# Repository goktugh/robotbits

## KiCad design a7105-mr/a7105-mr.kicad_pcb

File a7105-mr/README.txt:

A7105-MR

This board is a copy (reverse engineerd) of the MD7105-SY module
made by unknown Chinese company. No schematic is publicly available
so I've tried to copy the datasheet and the layout in the modules.

The reason for reverse engineering the board is to create a compatibe copy
with a much smaller crystal, as the original is absolutely huge.

I'm not completely sure what the board thickness needs to be, it is a thin 
pcb, either 0.8mm or 1.0mm (need to check with some calipers maybe?)

I don't know exactly what values all the capacitors / resistor / inductors are.
Finding the values is difficult because they are 0402 smd packages and mounted on the board.

The a7105 datasheet contains a schematic which is mostly similar to the one here. Some parts
are missed out though (presumably they are not needed, the original modules 
work properly, after all)

Two of the inductors are made using PCB traces (microstrip inductors) and
their inductance is very approximate.

A svg reverse engineering the board is in ../a7105_module

Sorry to whoever's intellectual property is taken with this, but I don't expect they
get much royalty anyway on a module which sells at < $2

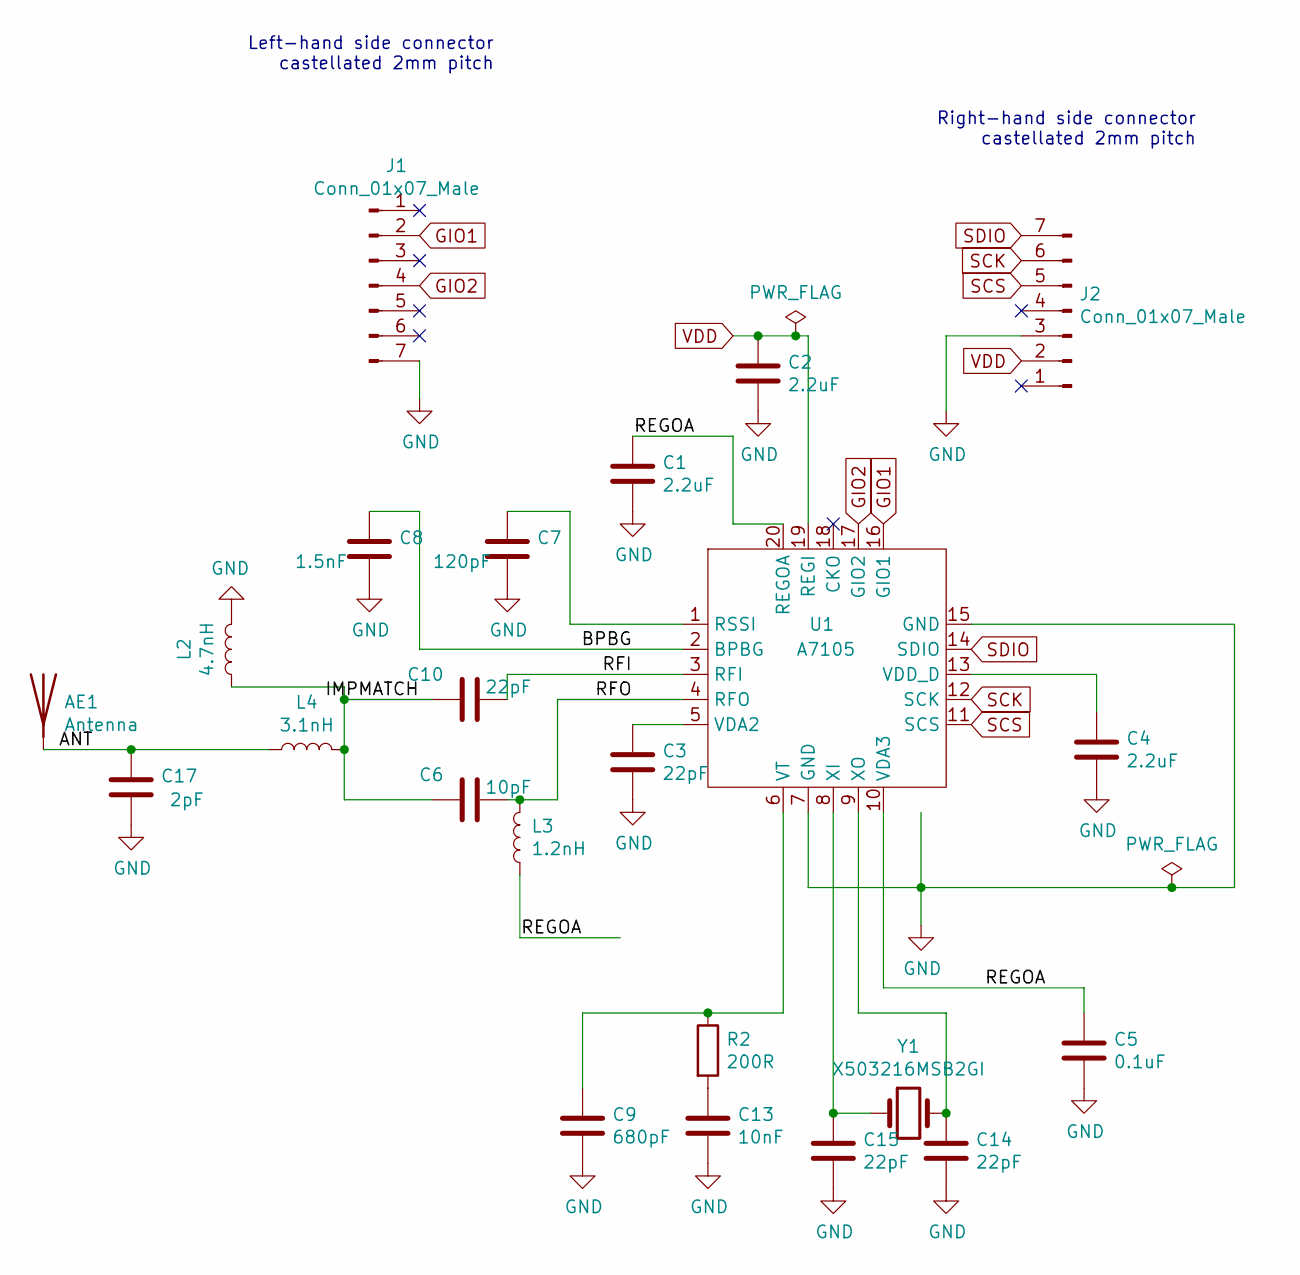
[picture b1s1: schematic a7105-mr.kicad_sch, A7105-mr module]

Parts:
AE1: Antenna; MIFA2
C1, C2, C4: 2.2uF; C_0402_1005Metric; LCSC C12530
C3, C10, C14, C15: 22pF; C_0402_1005Metric; LCSC C1555
C5: 0.1uF; C_0402_1005Metric; LCSC C1525
C6: 10pF; C_0402_1005Metric; LCSC C32949
C7: 120pF; C_0402_1005Metric; LCSC C76949
C8: 1.5nF; C_0402_1005Metric; LCSC C23967
C9: 680pF; C_0402_1005Metric; LCSC C307451
C13: 10nF; C_0402_1005Metric; LCSC C15195
C17: 2pF; C_0402_1005Metric; LCSC C1558
J1, J2: Conn_01x07_Male; castellatedpads_7
L2: 4.7nH; L_0402_1005Metric; LCSC C13595
L3: 1.2nH; mw_inductor_1nh
L4: 3.1nH; mw_inductor_3nh
R2: 200R; R_0402_1005Metric; LCSC C25087
U1: A7105; a7105-QFN-20; LCSC C126376
Y1: X503216MSB2GI; Crystal_SMD_5032-2Pin_5.0x3.2mm; LCSC C112572

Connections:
/ANT: AE1.1 (A), C17.1, L4.1
/BPBG: C8.1, U1.2 (BPBG)
/IMPMATCH: C6.1, C10.1, L2.1, L4.2
/REGOA: C1.1, C5.1, L3.1, U1.10 (VDA3), U1.20 (REGOA)
/RFI: C10.2, U1.3 (RFI)
/RFO: C6.2, L3.2, U1.4 (RFO)
GIO1: J1.2, U1.16 (GIO1)
GIO2: J1.4, U1.17 (GIO2)
GND: C1.2, C2.2, C3.2, C4.2, C5.2, C7.2, C8.2, C9.2, C13.2, C14.2, C15.2, C17.2, J1.7, J2.3, L2.2, U1.7 (GND), U1.15 (GND), U1.21 (GND)
unnamed: C3.1, U1.5 (VDA2)
unnamed: C4.1, U1.13 (VDD_D)
unnamed: C7.1, U1.1 (RSSI)
unnamed: C9.1, R2.1, U1.6 (VT)
unnamed: C13.1, R2.2
unnamed: C14.1, U1.9 (XO), Y1.2
unnamed: C15.1, U1.8 (XI), Y1.1
SCK: J2.6, U1.12 (SCK)
SCS: J2.5, U1.11 (SCS)
SDIO: J2.7, U1.14 (SDIO)
VDD: C2.1, J2.2, U1.19 (REGI)

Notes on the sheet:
Left-hand side connector castellated 2mm pitch
Right-hand side connector castellated 2mm pitch

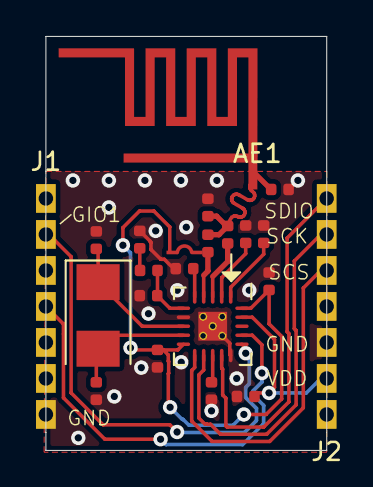
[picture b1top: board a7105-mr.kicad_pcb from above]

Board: 2 copper layers, 15.6 x 23.0 mm, 23 parts (0 on the bottom side), 20 nets.

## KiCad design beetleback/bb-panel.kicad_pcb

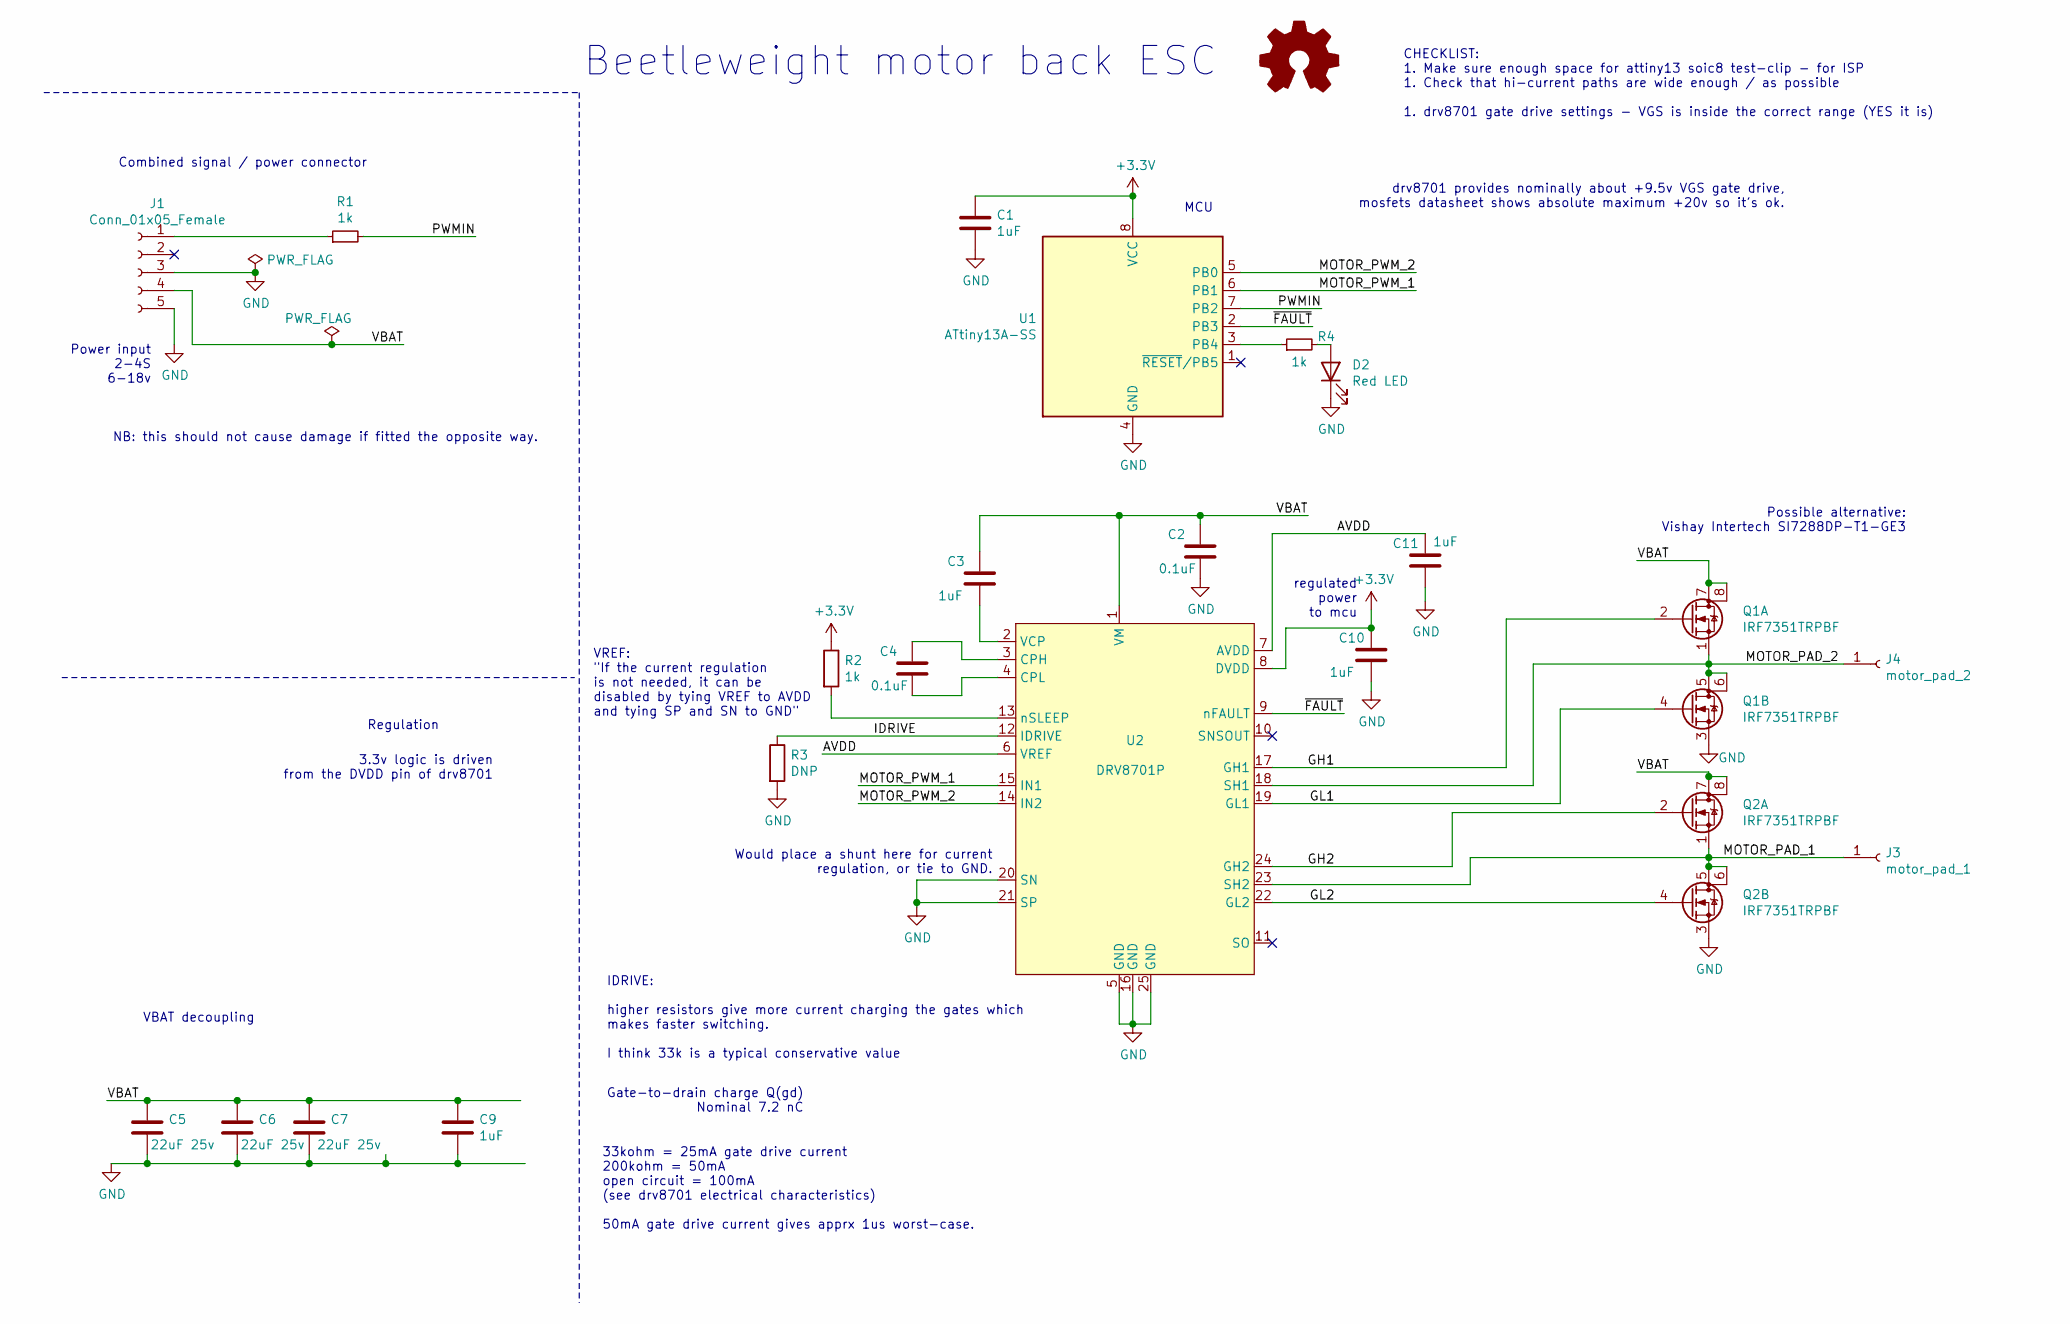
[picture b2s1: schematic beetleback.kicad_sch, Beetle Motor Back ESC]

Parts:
C1, C3, C9, C10, C11: 1uF; C_0402_1005Metric; LCSC C52923
C2, C4: 0.1uF; C_0402_1005Metric; LCSC C155422
C5, C6, C7: 22uF 25v; C_1206_3216Metric; LCSC C12891
D2: Red LED; LED_0603_1608Metric; LCSC C2286
J1: Conn_01x05_Female; JST_XH_B5B-XH-AM_doubleside; LCSC C161872
J3: motor_pad_1; bbb_motorpin
J4: motor_pad_2; bbb_motorpin
Q1, Q2: IRF7351TRPBF; SOIC-8_3.9x4.9mm_P1.27mm; LCSC C68403
R1, R2, R4: 1k; R_0402_1005Metric; LCSC C11702
R3: DNP; R_0603_1608Metric
U1: ATtiny13A-SS; SOIC-8_3.9x4.9mm_P1.27mm; LCSC C40382
U2: DRV8701P; VQFN-24-1EP_4x4mm_P0.5mm_EP2.45x2.45mm; LCSC C114178

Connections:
+3V3: C1.1, C10.1, R2.1, U1.8 (VCC), U2.8 (DVDD)
/AVDD: C11.1, U2.6 (VREF), U2.7 (AVDD)
/GH1: Q1.2 (G), U2.17 (GH1)
/GH2: Q2.2 (G), U2.24 (GH2)
/GL1: Q1.4 (G), U2.19 (GL1)
/GL2: Q2.4 (G), U2.22 (GL2)
/IDRIVE: R3.1, U2.12 (IDRIVE)
/MOTOR_PAD_1: J3.1, Q2.1 (S), Q2.5 (D), Q2.6 (D), U2.23 (SH2)
/MOTOR_PAD_2: J4.1, Q1.1 (S), Q1.5 (D), Q1.6 (D), U2.18 (SH1)
/MOTOR_PWM_1: U1.6 (PB1), U2.15 (IN1)
/MOTOR_PWM_2: U1.5 (PB0), U2.14 (IN2)
/PWMIN: R1.2, U1.7 (PB2)
/VBAT: C2.1, C3.1, C5.1, C6.1, C7.1, C9.1, J1.4, Q1.7 (D), Q1.8 (D), Q2.7 (D), Q2.8 (D), U2.1 (VM)
/~FAULT: U1.2 (PB3), U2.9 (nFAULT)
GND: C1.2, C2.2, C5.2, C6.2, C7.2, C9.2, C10.2, C11.2, D2.1 (K), J1.3, J1.5, Q1.3 (S), Q2.3 (S), R3.2, U1.4 (GND), U2.5 (GND), U2.16 (GND), U2.20 (SN), U2.21 (SP), U2.25 (GND)
unnamed: C3.2, U2.2 (VCP)
unnamed: C4.1, U2.3 (CPH)
unnamed: C4.2, U2.4 (CPL)
unnamed: D2.2 (A), R4.2
unnamed: J1.1, R1.1
unnamed: R2.2, U2.13 (nSLEEP)
unnamed: R4.1, U1.3 (PB4)
no_connect_23: J1.2
no_connect_24: U1.1 (~RESET~/PB5)
no_connect_25: U2.10 (SNSOUT)
no_connect_26: U2.11 (SO)

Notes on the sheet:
Power input 2-4S 6-18v
VBAT decoupling
Combined signal / power connector
Regulation
3.3v logic is driven from the DVDD pin of drv8701
NB: this should not cause damage if fitted the opposite way.
VREF: "If the current regulation is not needed, it can be disabled by tying VREF to AVDD and tying SP and SN to GND"
33kohm = 25mA gate drive current 200kohm = 50mA open circuit = 100mA (see drv8701 electrical characteristics) 50mA gate drive current gives apprx 1us worst-case.
IDRIVE: higher resistors give more current charging the gates which makes faster switching. I think 33k is a typical conservative value
Gate-to-drain charge Q(gd) Nominal 7.2 nC
Would place a shunt here for current regulation, or tie to GND.
MCU
Beetleweight motor back ESC
regulated power to mcu
CHECKLIST: 1. Make sure enough space for attiny13 soic8 test-clip - for ISP 1. Check that hi-current paths are wide enough / as possible 1. drv8701 gate drive settings - VGS is inside the correct range (YES it is)
drv8701 provides nominally about +9.5v VGS gate drive, mosfets datasheet shows absolute maximum +20v so it's ok.
Possible alternative: Vishay Intertech SI7288DP-T1-GE3

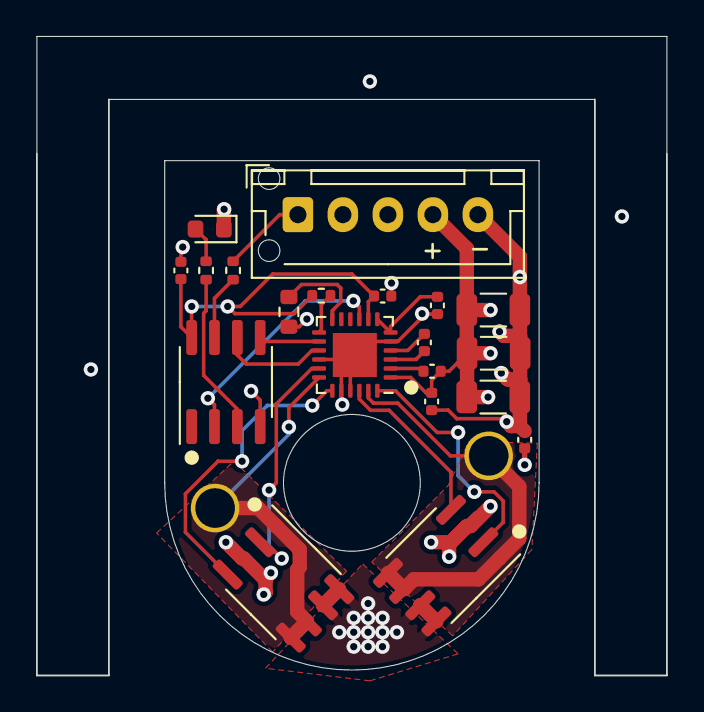
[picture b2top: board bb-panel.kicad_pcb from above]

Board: 4 copper layers, 35.0 x 35.5 mm, 22 parts (0 on the bottom side), 22 nets.

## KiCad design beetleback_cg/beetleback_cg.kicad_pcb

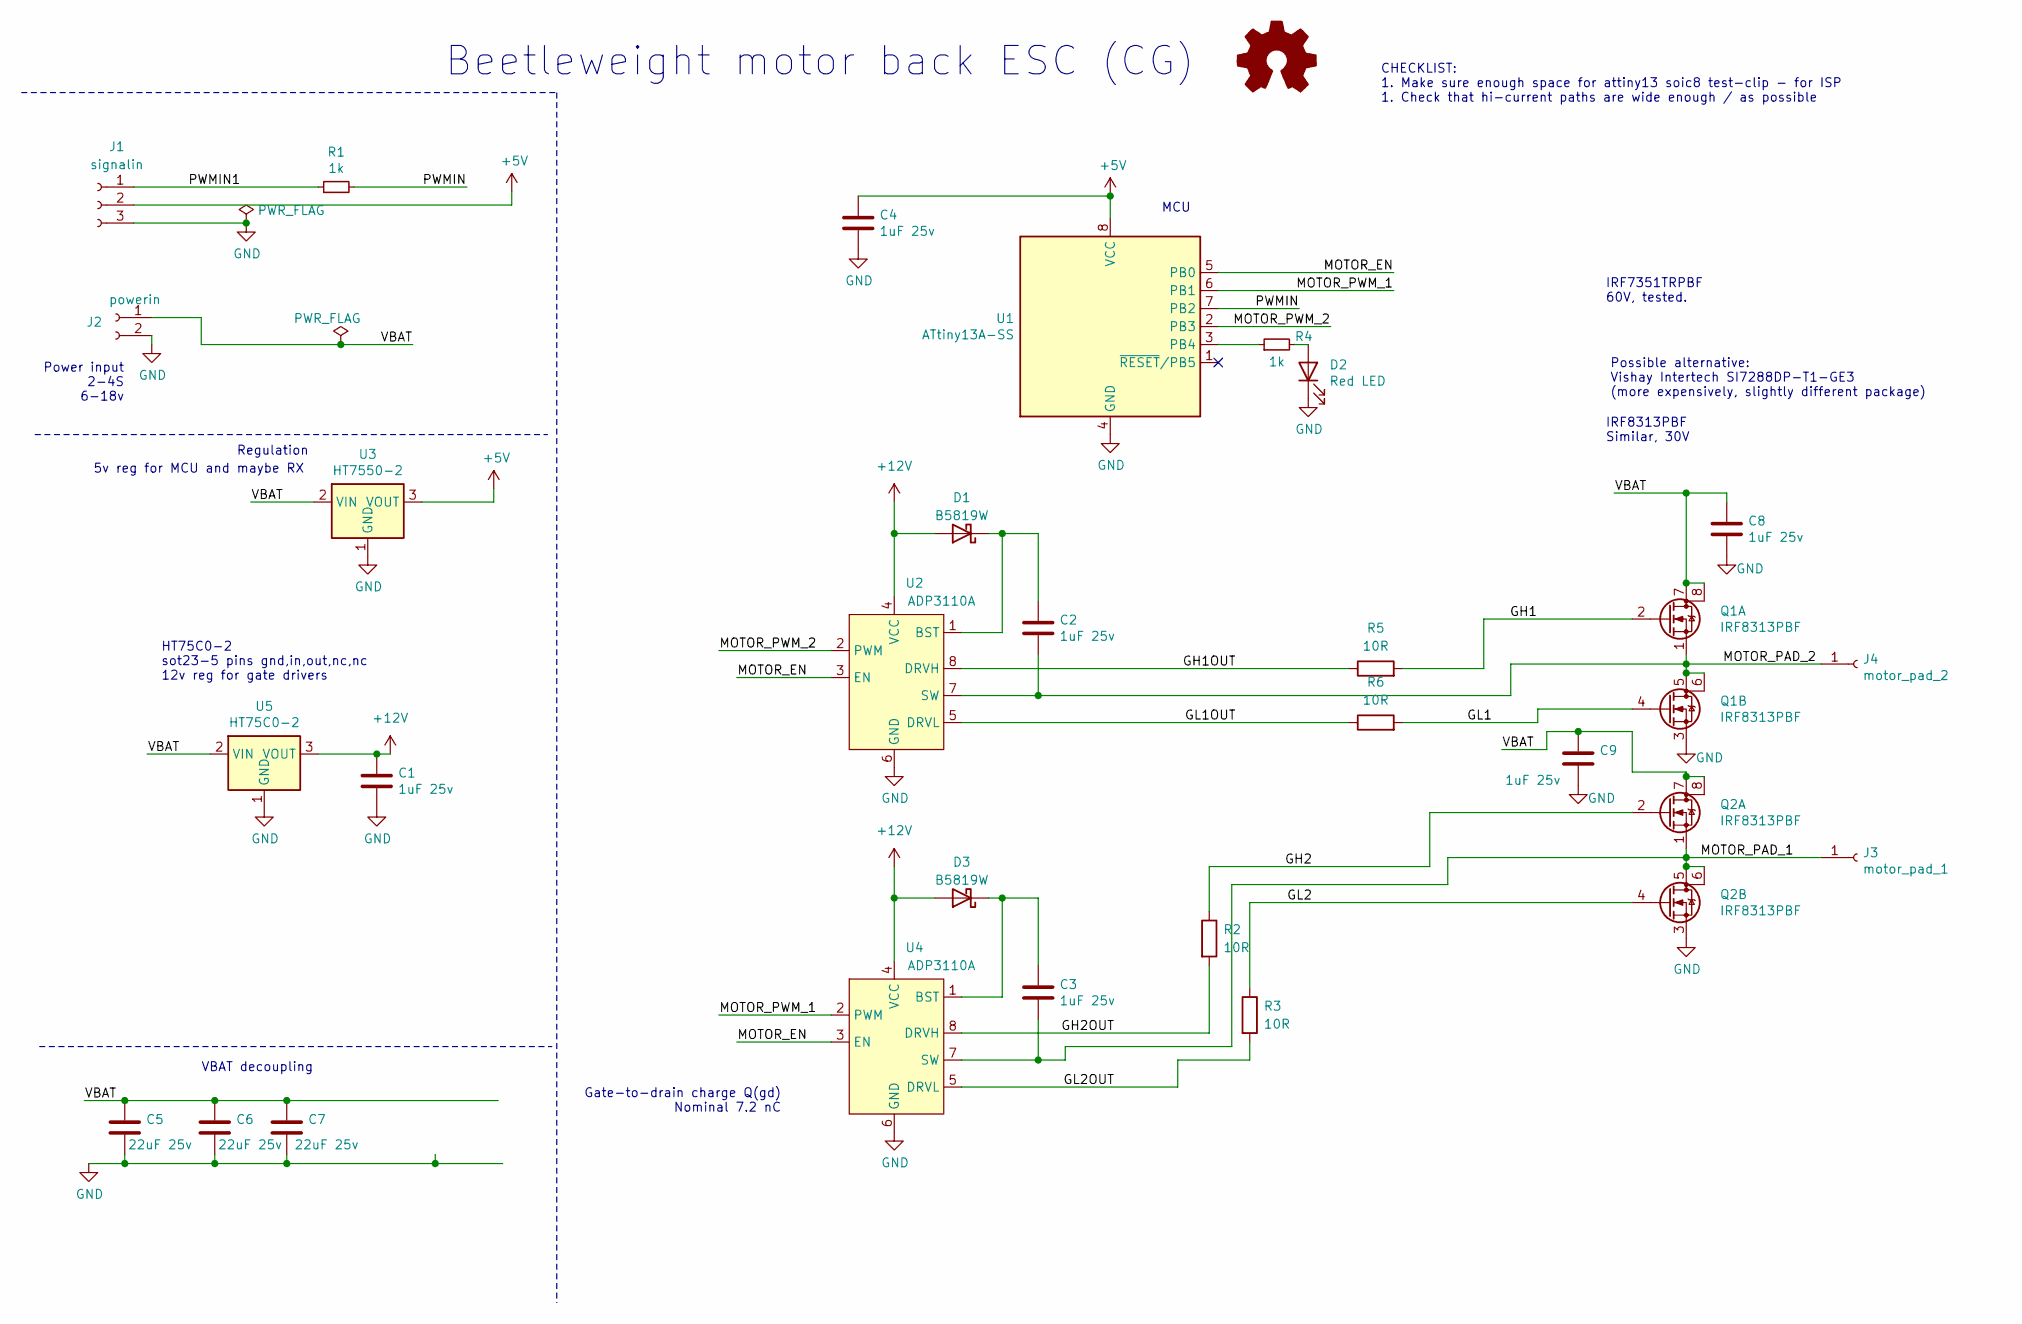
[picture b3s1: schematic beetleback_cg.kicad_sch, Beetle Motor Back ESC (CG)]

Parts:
C1, C2, C3, C4, C8, C9: 1uF 25v; C_0402_1005Metric; LCSC C52923
C5, C6, C7: 22uF 25v; C_1206_3216Metric; LCSC C12891
D1, D3: B5819W; D_SOD-123; LCSC C8598
D2: Red LED; LED_0603_1608Metric; LCSC C2286
J1: signalin; PinHeader_1x03_P2.54mm_Vertical
J2: powerin; SolderWire-1sqmm_1x02_P5.4mm_D1.4mm_OD2.7mm
J3: motor_pad_1; bbb_motorpin
J4: motor_pad_2; bbb_motorpin
Q1, Q2: IRF8313PBF; SOIC-8_3.9x4.9mm_P1.27mm; LCSC C57696
R1, R4: 1k; R_0402_1005Metric; LCSC C11702
R2, R3, R5, R6: 10R; R_0402_1005Metric; LCSC C25077
U1: ATtiny13A-SS; SOIC-8_3.9x4.9mm_P1.27mm; LCSC C14075
U2, U4: ADP3110A; SOIC-8_3.9x4.9mm_P1.27mm; LCSC C82321
U3: HT7550-2; SOT-23-5; LCSC C81799
U5: HT75C0-2; SOT-23-5; LCSC C95005

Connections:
+5V: C4.1, J1.2, U1.8 (VCC), U3.3 (VOUT)
+12V: C1.1, D1.2 (A), D3.2 (A), U2.4 (VCC), U4.4 (VCC), U5.3 (VOUT)
/GH1: Q1.2 (G), R5.2
/GH1OUT: R5.1, U2.8 (DRVH)
/GH2: Q2.2 (G), R2.1
/GH2OUT: R2.2, U4.8 (DRVH)
/GL1: Q1.4 (G), R6.2
/GL1OUT: R6.1, U2.5 (DRVL)
/GL2: Q2.4 (G), R3.1
/GL2OUT: R3.2, U4.5 (DRVL)
/MOTOR_EN: U1.5 (PB0), U2.3 (EN), U4.3 (EN)
/MOTOR_PAD_1: C3.2, J3.1, Q2.1 (S), Q2.5 (D), Q2.6 (D), U4.7 (SW)
/MOTOR_PAD_2: C2.2, J4.1, Q1.1 (S), Q1.5 (D), Q1.6 (D), U2.7 (SW)
/MOTOR_PWM_1: U1.6 (PB1), U4.2 (PWM)
/MOTOR_PWM_2: U1.2 (PB3), U2.2 (PWM)
/PWMIN: R1.2, U1.7 (PB2)
/PWMIN1: J1.1, R1.1
/VBAT: C5.1, C6.1, C7.1, C8.1, C9.1, J2.1, Q1.7 (D), Q1.8 (D), Q2.7 (D), Q2.8 (D), U3.2 (VIN), U5.2 (VIN)
GND: C1.2, C4.2, C5.2, C6.2, C7.2, C8.2, C9.2, D2.1 (K), J1.3, J2.2, Q1.3 (S), Q2.3 (S), U1.4 (GND), U2.6 (GND), U3.1 (GND), U4.6 (GND), U5.1 (GND)
unnamed: C2.1, D1.1 (K), U2.1 (BST)
unnamed: C3.1, D3.1 (K), U4.1 (BST)
unnamed: D2.2 (A), R4.2
unnamed: R4.1, U1.3 (PB4)

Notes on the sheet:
Power input 2-4S 6-18v
HT75C0-2 sot23-5 pins gnd,in,out,nc,nc 12v reg for gate drivers
5v reg for MCU and maybe RX
Regulation
VBAT decoupling
Gate-to-drain charge Q(gd) Nominal 7.2 nC
MCU
Beetleweight motor back ESC (CG)
CHECKLIST: 1. Make sure enough space for attiny13 soic8 test-clip - for ISP 1. Check that hi-current paths are wide enough / as possible
IRF7351TRPBF 60V, tested.
IRF8313PBF Similar, 30V
Possible alternative: Vishay Intertech SI7288DP-T1-GE3 (more expensively, slightly different package)

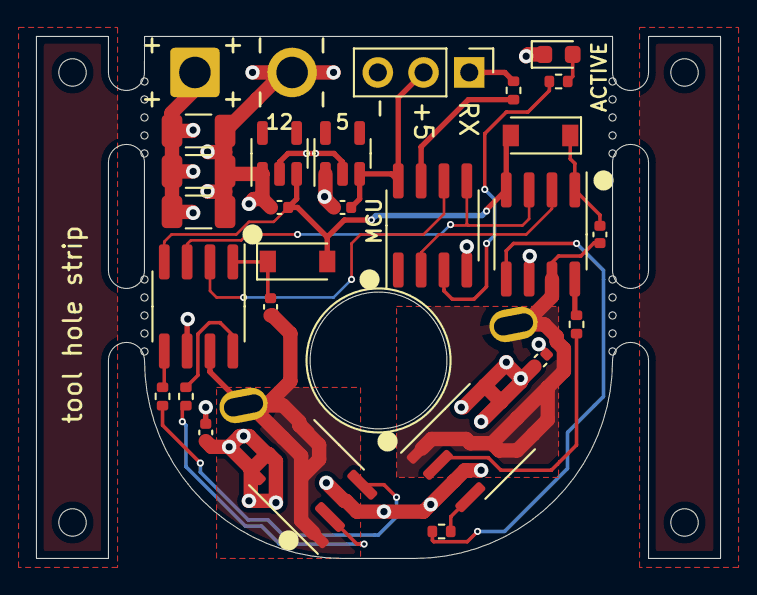
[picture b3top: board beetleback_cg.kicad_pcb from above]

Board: 4 copper layers, 38.0 x 29.0 mm, 29 parts (0 on the bottom side), 23 nets.

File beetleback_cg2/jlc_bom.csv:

Comment,Designator,Footprint,LCSC
ATtiny13A-SS,"U1",Package_SO:SOIC-8_3.9x4.9mm_P1.27mm,C14075
HT7550-2,"U3",Package_TO_SOT_SMD:SOT-23-5,C81799
22uF 25v,"C5,C6,C7",Capacitor_SMD:C_1206_3216Metric,C12891
IRF8313PBF,"Q2,Q1",Package_SO:SOIC-8_3.9x4.9mm_P1.27mm,C57696
HT75C0-2,"U5",Package_TO_SOT_SMD:SOT-23-5,C95005
10R,"R5,R6,R3,R2",Resistor_SMD:R_0402_1005Metric,C25077
1uF 25v,"C1,C2,C4,C9,C3,C8",Capacitor_SMD:C_0402_1005Metric,C52923
B5819W,"D1,D3",Diode_SMD:D_SOD-123,C8598
ADP3110A,"U2,U4",Package_SO:SOIC-8_3.9x4.9mm_P1.27mm,C82321
1k,"R1,R4",Resistor_SMD:R_0402_1005Metric,C11702
Red LED,"D2",LED_SMD:LED_0603_1608Metric,C2286
